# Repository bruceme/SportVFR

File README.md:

# SportVFR

!CATION! - Continued work in progress

An open-source DIY flight instrument

Early Prototype (will post updates once v2 is ready, early April 2025)

# V0.3 Update (1/21/2026)

The most obvious and immediate change is that I switched to the higher speed and higher GPIO pin count on the STM32F103 "Blue Pill".

From feedback, I built a 3-1/8" Round version of the SportVFR, it's built from the identical schematic as the rectangular version. 

I'm preparing to build a flying version, which is an engine monitor only for now.  I will add the airspeed, compass, and altimeter soon, but focusing on the engine sensors and monitoring allows me to finalize them.

I struggled with the configuration so much that I just removed it for now.  It will work for the exact engine sensors I have, if you need to tweak the coefficients for your sensors or use different kinds of sensors, you'll have to change the code for now.  I am thinking about techniques for accommodating various sensors in the hardware and software, but for now, I'm keeping it simple.

Sensors... A constant struggle.  I have settled on a few basic things around sensors.

Fuel Quantity Sensors - Low impedance resistive.  They use a precision op-amp to convert low-current/voltage signals into the analog 0-3.3v signal for the ADC.  I have 4 channels of op-amps.

Oil Temperature - I'm using the Westech oil temp sensor.  It reads 10k-Ohms at 0C, 1.6k Ohms at 39C, 212 Ohms at 100C.  This is easily a low current (0.5ma @ 120C/250F) with a simple voltage divider using a high-precision pull-up resistor.  The code interpolates the logarithmic temperature response curve to give highly accurate temperatures.

Oil Pressure / Fuel Pressure - I use 3-wire pressure sensors; they are much easier to handle and just return voltages from 0.3 - 2.7v using a 3.3v source.  Super simple, also curve-fit-interpolated by the code from measured data.

Outside Air Temp - I used a Dallas one-wire temperature probe.  It's a digital response and highly accurate from -20C - 100C.  I 3d printed a fuse-skin mounting bracket.

The Tachometer and Fuel Flow are both pulse count sensors.  This is best done using the built-in hardware clock timers, the code is well documented.  This is not yet tested, and I'm sure there will be tweaks as I get into real-world testing. 

# V0.2 Update (3/31/2025)

I've been doing a lot of work on this, and I've made several big improvements.

New Wiring Diagram

1. There's now a DSub-15 pinout with more grounds. unfortunately, couldn't add all the 5V-Out for sensor power needed; there's just one.
1. Using op-amps to measure resistance sensors (OT, FQ1, FQ2), better all around
1. Integrated the magnetometer and absolute pressure sensors into the board design.  This lowers the project cost and makes the BOM smaller and the project simpler to build.
1. I've tested every sensor/instrument and gotten them all working
1. Code changes
 - Lots of simple fixes
 - Sensor-read-skip.  There's 7+ sensors to ready now, It's best to kkin sensor reads each cycle so the slow sensor reads update less frequently than the page display, big performance boost.
 - Created a fuel quantity page

# V0.3 Updates (tbd)

1. DSub25 with more grounds and 5v-Out for sensors
2. Aux1-5 with Aux1 pre-conditioned for low impedence sensors (another fuel quantity, etc)
3. Fuel Flow sensor added

# The Project

## Engine/Aircraft System Data Acquisition
There are only 8 analog input channels. That is limiting, but can support all required inputs;
  
|                          | Interface         | Sensor     |
|--------------------------|-------------------|------------|
| Airspeed                 | Serial - I2C      | ABPMRRV060MG2A3 |
| Altitude                 | Serial - I2C      | GZP6816D |
| Compass                  | Serial - I2C      | TLV493DA1B6HTSA2 |
| Engine RPM               | Counter 0-5v | Direct Messure  |
| Oil Temperature          | Analog Resistive  | Low-Impedence Amp  |
| Oil Pressure             | 0-5v  | 5V Pressure Gauge  |
| Fuel Pressure            | 0-5v  | 5V Pressure Gauge  |
| Fuel Quantity, each tank | Analog Resistive  | Low-Impedence Amp |
| Fuel Flow 		   | Counter 0-5v  | BM8563 |
| Tach Hour Meter	   | Uses Tach and time|            |

## BOM

### MCU - "Pro Micro atmega32u4"

### Compass and Altitude
  Built into the board

### Air Pressure sensors
[ABPMRRV060MG2A3](https://www.mouser.com/ProductDetail/Honeywell/ABPMRRV060MG2A3?qs=OTrKUuiFdkZ2B8eiLukmLQ%3D%3D)

*Alternatives (will require coding):*
- PX4 Airspeed Module (MS4525DO is the sensor)
- MPXV7002DP - This is a differential analog and may require amplification

### Engine Sensors

- Tach: This is a 2-pulse per rotation 12v signal coming from my Magnetos, it's voltage split to 0-5v.  You can change the number of pulses in the code.
- Oil Temp, Oil Pressure, Fuel Pressure, Fuel Quantity : These are all resistivity sensors with a typical operating range of 0-5kohm.  You can use any sensors that work on your engine.  You will need to calibrate them in the code.
  
### Display
HD44780 -I2C 1602 Character LCD Display

### Input
Rotary Encoder (CYT1100), usually comes with a small knob

### Alert LED
10mm Red LED

## Typical cost break-down (Spring 2025)

| Sport VFR             |             |         |
| --------------------- | ----------- | ------- |
|                       | Source      | Amount  |
| PCB Board             | email me    | $4.50  |
| Case                  | thingiverse | $10.00  |
| ProMicro              | Jungle      | $7.00   |
| Airspeed              | Mouser      | $35.00  |
| Rotary Encoder        | Jungle      | $0.56   |
| Alert LED / Resistors | Jungle      | $0.10   |
|                       |             |         |
|                       | Sub-Total   | $57.16  |
|                       |             |         |
| Sample Sensor BOM     |             |         |
|                       |             |         |
| Oil Pressure          | Jungle      | $14.68  |
| Oil Temperature       | Jungle      | $18.55  |
| Fuel Pressure         | Jungle      | $23.99  |
| Fuel Quantity x2      | Jungle      | $59.98  |
|                       |             |         |
|                       | Sub-Total   | $117.20 |
|                       |             |         |
| Total. System Cost    |             | $174.36 |

## The build

The [SportVFR v0.2 Board](scheamtic/SportVFR.0.0.2.zip) contains the Gerber files. These can be fabricated by multiple vendors.  My run of 5 was $20 shipped.  Most components are through-hole, but some are "large" format surface mounts that can be soldered by hand with medium soldering skills.  Installing the DB-9 right-angle connector is preferred so you can remove the display quickly later to work on your panel, but you may directly solder the input wires to the through-holes.

For the case, print it yourself or send it out.  It does require 4 6x8mm "threadserts" and M3 screws to mount to the panel.

## Testing and Calibration

!CATION! - Work in progress (see updates coming soon)

Once assembled and connected to sensors you will need to calibrate the system to your sensors.  This is done by compiling to the calibration mode and recording various values at known sensor points.  Please note the calibrations are unitless, you can use whatever units you want, so long as you remember them. Typical US units would be knots, gallons, psi and Fahrenheit... But you could calibrate in kph, liters, mPa and C or any combination so long as the numbers displayed on the screen make sense to you.

Calibration points/ commands are:

You enter compass calibration mode by holding down the encoder button while powering up the unit.  From there you'll be prompted to move the plane in a circle... just follow the prompts.

NOTE: When the in-code varaibles is set to "InCalibrationMode = true" The display is outputing raw values.  The layout is similar to but not identical to the normal display mode in order to show all sensors outputs.  It as as follows:
| Airspeed              | Heading  	| Altitude    |	 Up/down   |
| --------------------- | ----------- 	| ----------- |----------  |
| Tachometer 		| Oil Temp      | Oil Press   | Fuel Press | 

How to calibrate various sensors:  This calibration requires you to record values from the unconfigured device and enter them into the code.  You can always re-run these test by setting "InCongig" true and the values will get displayed.

- Airspeed: Read the zero pressure at rest.  Using a hose connected to the top tube of the airspeed sensor, have someone drive you a known speed and record that speed it to that speed.  Enter those values for AirspeedZero and Airspeed60
- Altimeter: Lookup the altitude of your current location.  Set the barometeric pressure to the closest known source and set the altitude in configuraton mode.
- Tachometer: Look up PulsesPerRPM in the code and set that to tachometer source. 
- Oil Temp: Set out a bowl of ice water and get a pot of boiling water, you'll use these test points to calibrate the temperature sensor.  Take the numbers displayed and put them into the code for OilTempMin and OilTempMax
- Oil Pressure & Fuel Pressure: Set the zero pressure at rest.  If your sensors have NPT (nation pipe thread) fittings, they will likely fit directly into a standard compressor hose.  Fill your tank to a known pressure within the range of the sensor and set it to that.  Take the numbers displayed and put them into the code as Oil/Fuel Pressure Min & Max.

# Future thoughts...

## Display or Not Display? That is the question. 

One could easily built an entire dedicated flight information display system (EFIS/ECAM) around this platform.

Or... You could say that any phone or tablet is a perfectly robust flight display system and what if you just focussed on all the data a phone/tablet can't get easily.  Airspeed, Compass, Engine, System sensors, etc.  The project needs to be integrated with a bluetooth transciever (HC-05).  Updates can easily be made to Avare for Android.  At some point compatability with other IMUs would be good so more wide adoption can be considered.

I honestly like both ideas but I lean toward the later as it's simpler and more direct.  Either way, I'd like to leave this project open-ended and not make any decisions that presuppose a display system.  

## IMU Considerations

* Sensors 
	The checked in code uses a HMC5883. The MPU9250 is newer, I would substitute.  This is a  raw output sensor and requires pretty complex 4-dof (quaternion) summing to output useful attitude data.  The altitude pressure sensor are adiquate and usually come with the attitude module.
* Cleanflight / Naze32 upgrade?
	  The Naze32 quad IMU is a nice complete inertia system with tons of great support from the quad copter community.  I have some great success setting it up in aircraft mode and interfacing via serial MultiWii protocol. It output all attitude and altitude data raw with very fast refresh.  It also supports GPS.

## AoA
    A sensitive airspeed sensor could be added for AoA and interface similarly to the airspeed

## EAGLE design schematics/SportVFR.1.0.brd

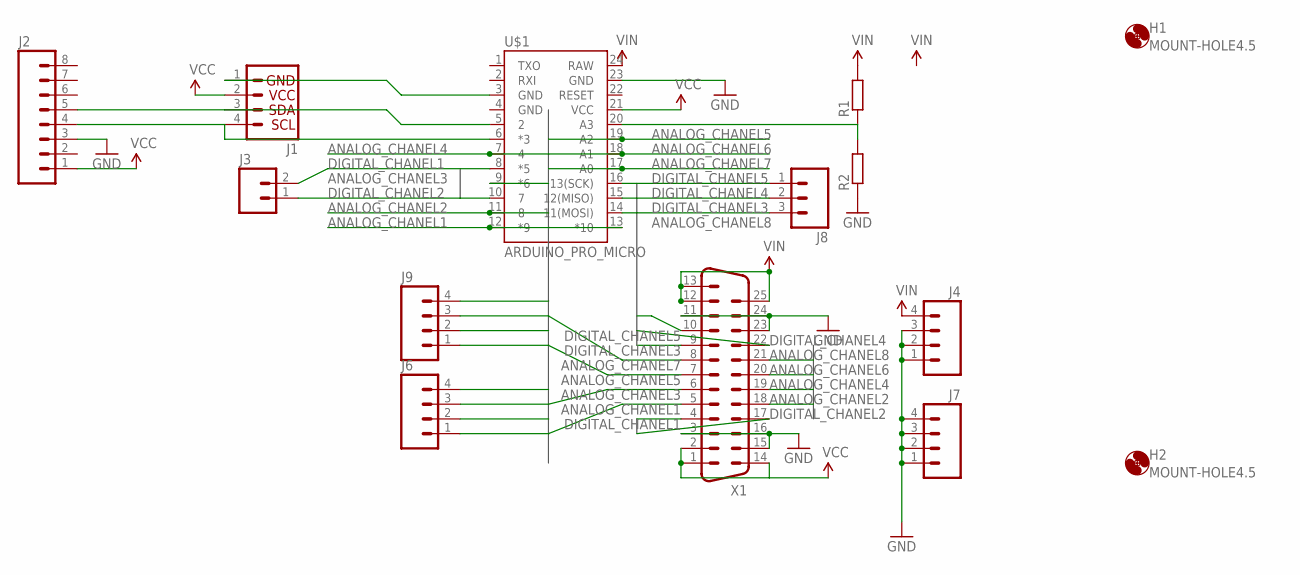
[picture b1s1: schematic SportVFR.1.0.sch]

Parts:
H1, H2: MOUNT-HOLE4.5; 4,5
J1: I2C_STANDARD; 1X04
J2: M08SILK_FEMALE_PTH; 1X08
J3: M02PTH; 1X02
J4, J6, J7, J9: M04PTH; 1X04
J8: M03PTH; 1X03
R1, R2: R-EU_R0805; R0805
U$1: ARDUINO_PRO_MICRO
X1: DB25HP; M25HP

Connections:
ANALOG_CHANEL1: J6.1, U$1.12 (*9), X1.5
ANALOG_CHANEL2: J6.2, U$1.11 (8), X1.18
ANALOG_CHANEL3: J6.3, U$1.9 (*6), X1.6
ANALOG_CHANEL4: J6.4, U$1.7 (4), X1.19
ANALOG_CHANEL5: J9.1, U$1.19 (A2), X1.7
ANALOG_CHANEL6: J9.2, U$1.18 (A1), X1.20
ANALOG_CHANEL7: J9.3, U$1.17 (A0), X1.8
ANALOG_CHANEL8: J9.4, U$1.13 (*10), X1.21
DIGITAL_CHANEL1: J3.2, U$1.8 (*5), X1.4
DIGITAL_CHANEL2: J3.1, U$1.10 (7), X1.17
DIGITAL_CHANEL3: J8.3, U$1.14 (11(MOSI)), X1.9
DIGITAL_CHANEL4: J8.2, U$1.15 (12(MISO)), X1.22
DIGITAL_CHANEL5: J8.1, U$1.16 (13(SCK)), X1.10
GND: J2.3, J4.1, J4.2, J4.3, J7.1, J7.2, J7.3, J7.4, R2.1, U$1.23 (GND), X1.3, X1.11, X1.15, X1.16, X1.23, X1.24
unnamed: J1.3, J2.5, U$1.5 (2)
unnamed: J1.4, J2.4, U$1.6 (*3)
unnamed: J1.1, U$1.3 (GND)
unnamed: R1.1, R2.2, U$1.20 (A3)
VCC: J1.2, J2.1, U$1.21 (VCC), X1.1, X1.2, X1.14
VIN: J4.4, R1.2, U$1.24 (RAW), X1.12, X1.13, X1.25

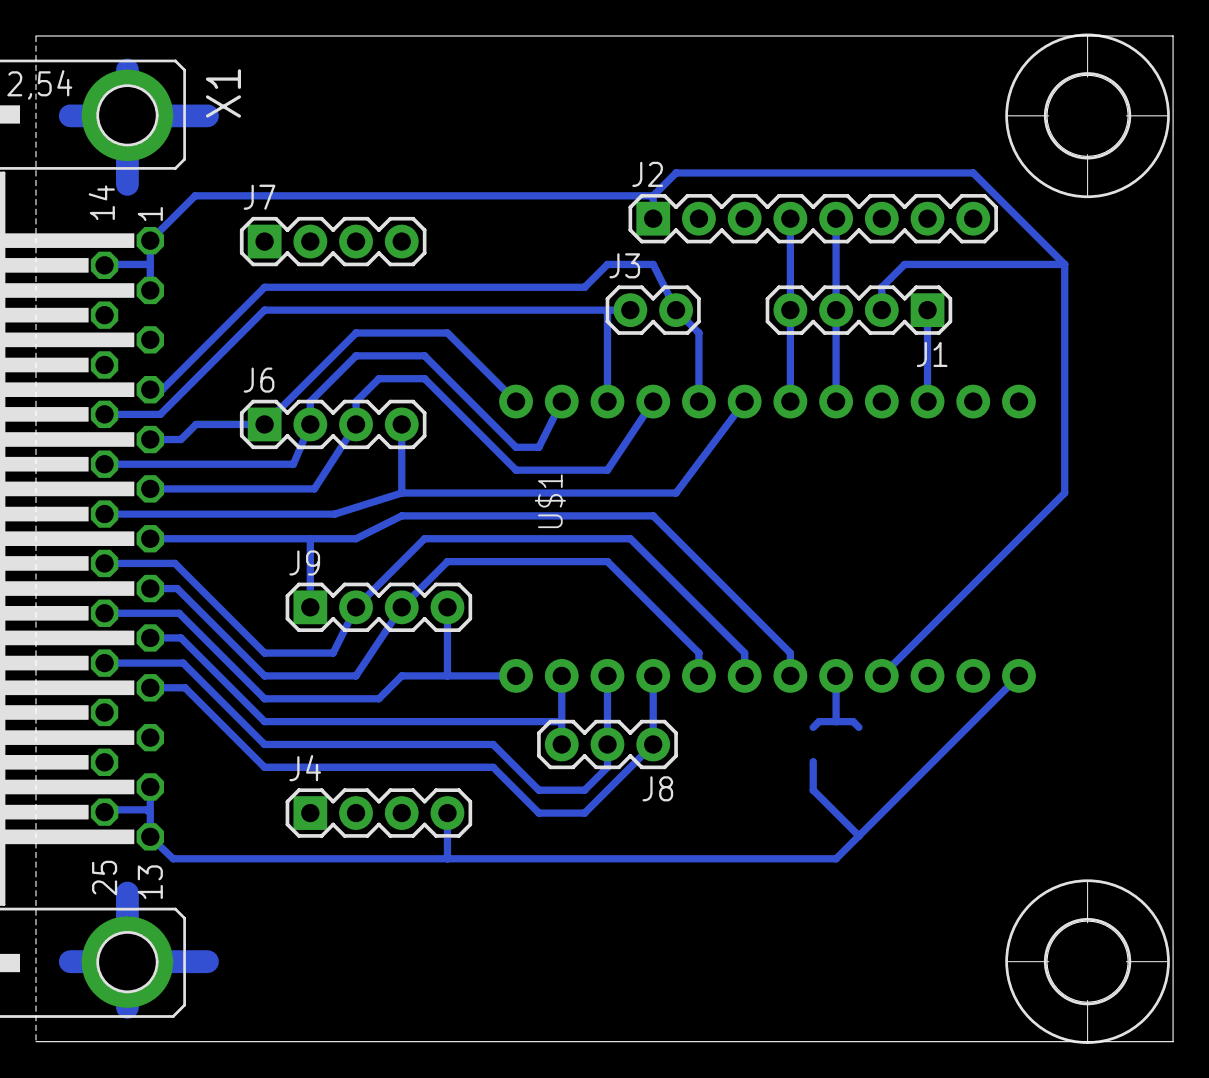
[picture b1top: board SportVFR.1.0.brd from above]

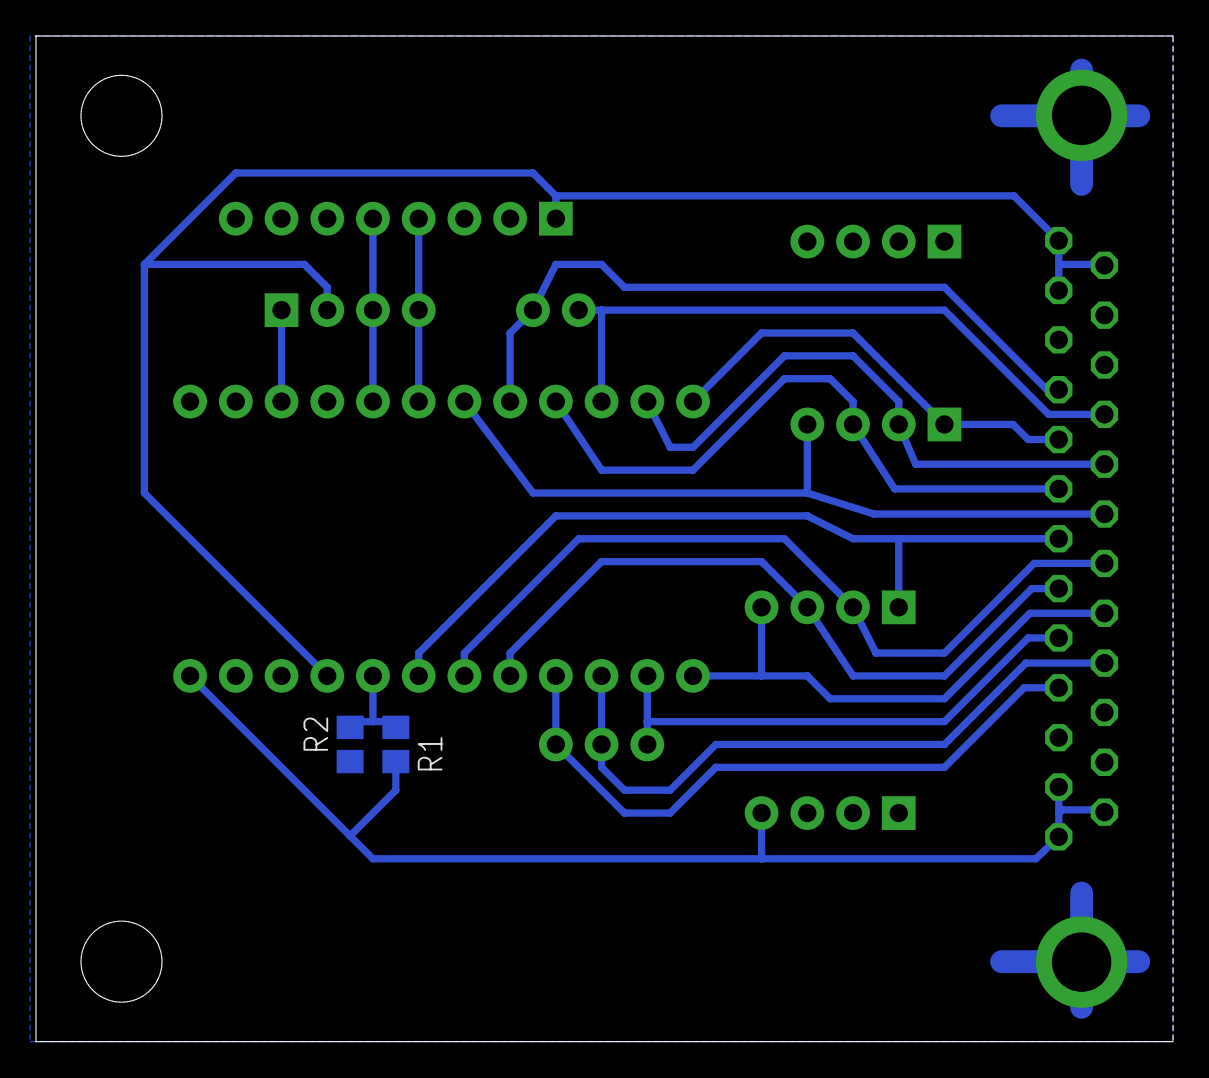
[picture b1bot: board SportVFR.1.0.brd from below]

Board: 2 copper layers, 63.2 x 55.9 mm, 14 parts (2 on the bottom side), 20 nets.

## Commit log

2015-11-21 Create SportVFR,ino
2018-01-04 added schematics
2018-01-04 Added Bom
2025-03-19 Added images and tweaked content
2025-03-19 First case prorotype photo
2025-03-23 Lots of changes... Ported to VSCode/PlatformIO
2025-03-23 Update README.md
    Updated the config section
2025-03-24 Cleaned up instruments and added support for ADP sensor
2025-03-31 Updated sensors, better modes, added amps, lots of pins
2026-01-21 Engine Monitor Prep
2026-01-21 Revise README with V0.3 update and project status
    Updated project status and detailed V0.3 changes regarding hardware and sensor configurations.
2026-01-21 oat and bracket
2026-01-21 Round
2026-01-21 Update README with new images and V0.3 details
    Added images for the SportVFR project and updated version details.
2026-01-21 Change image file extensions in README
    Updated image file extensions from .jpeg to .jpg for consistency.
2026-01-21 Replace image tags with HTML for better formatting
    Updated images for SportVFR project and modified text.
2026-03-03 closer to done
2026-03-03 fixed oil temp

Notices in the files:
parts and their libraries:
SparkFun-Connectors: Licensing: Creative Commons ShareAlike 4.0 International - https://creativecommons.org/licenses/by-sa/4.0
